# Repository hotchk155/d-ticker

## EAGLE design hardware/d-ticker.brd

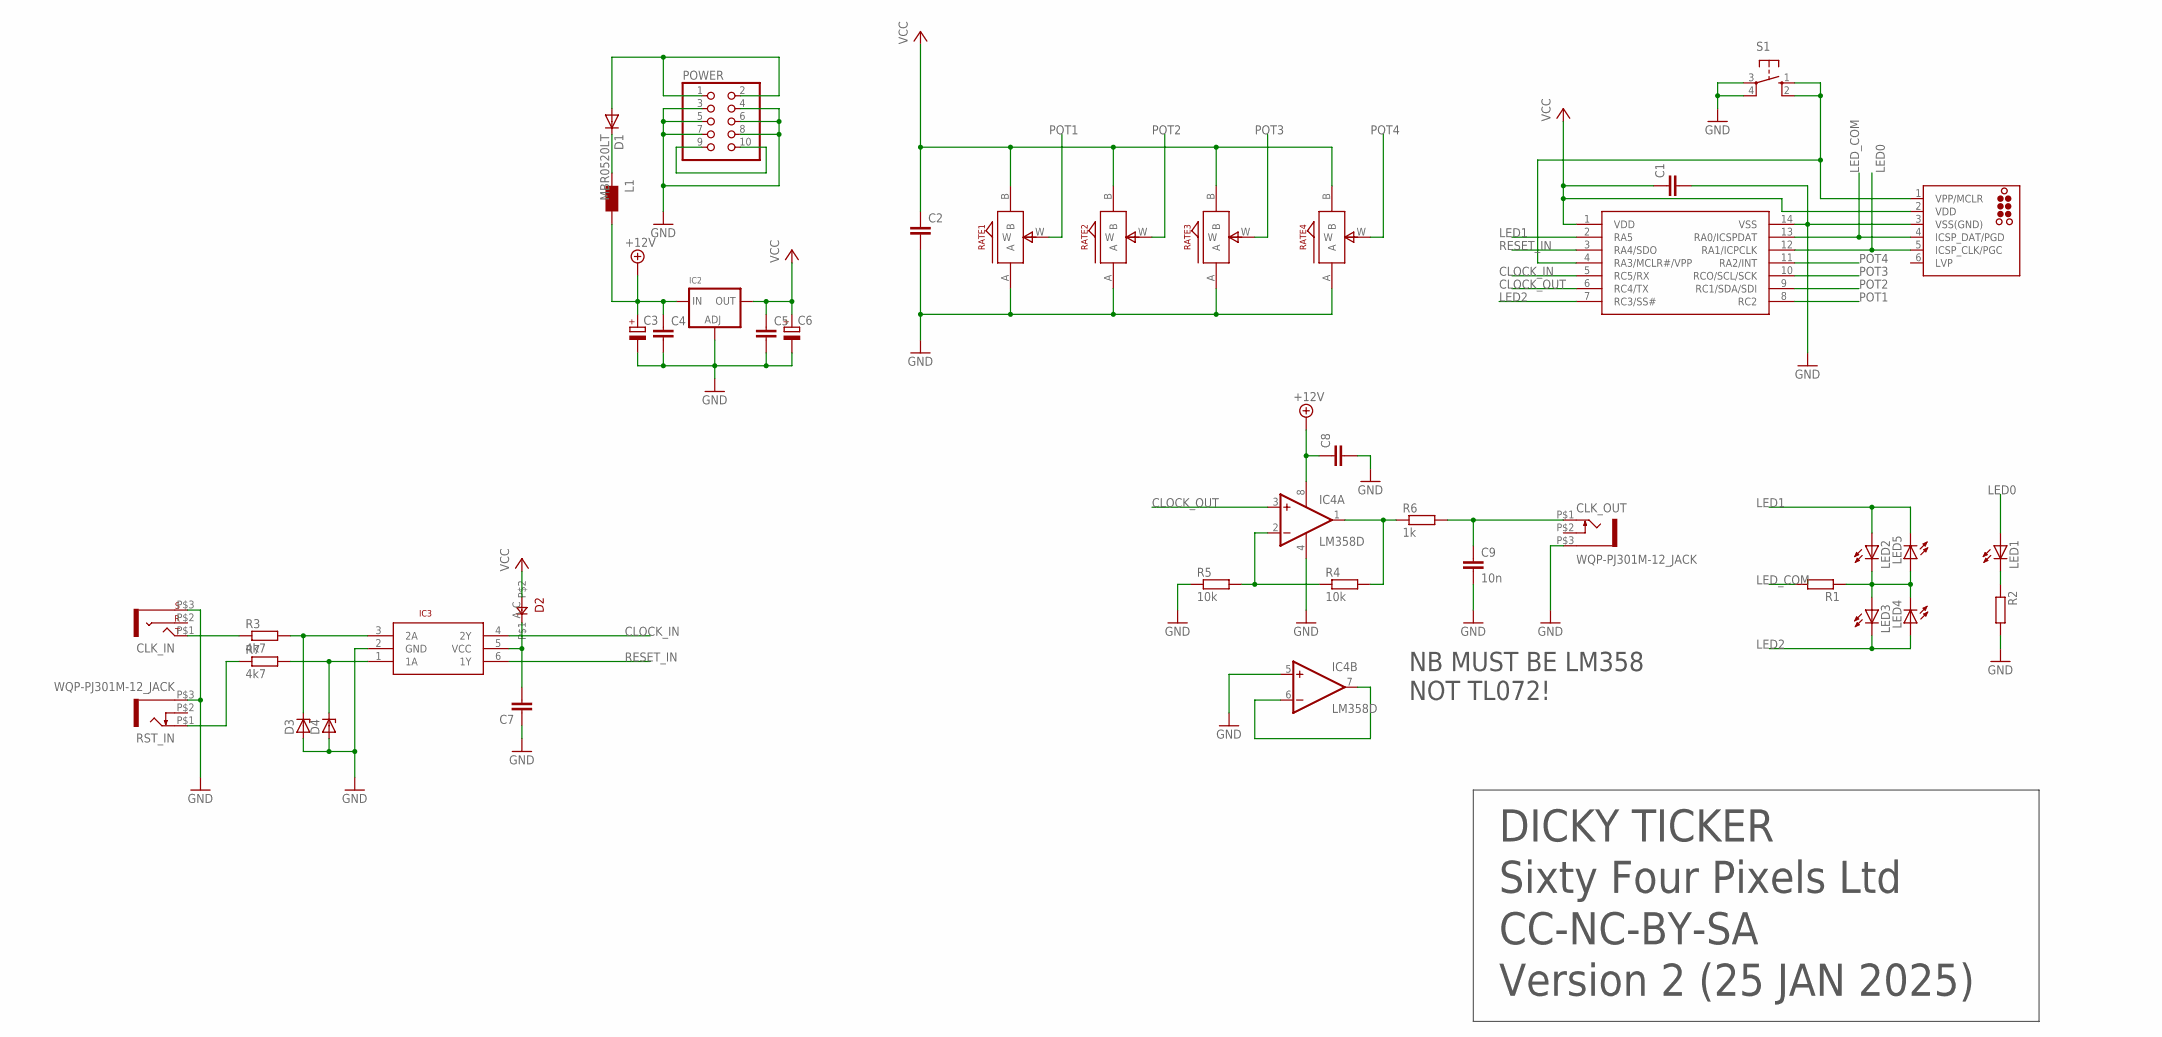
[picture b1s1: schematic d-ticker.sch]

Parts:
C1, C2, C4, C5, C7, C8: C-EUC0805; C0805
C3, C6: CPOL-EUSMCA; SMC_A
C9: 10n; C0805
CLK_IN: THONKICONN_STEREO; WQP-PJ301M-ST
CLK_OUT: WQP-PJ301M-12_JACK
D1: MBR0520LT; SOD123
D2: 0805DIODE
D3, D4: ZENER-DIODESOD80C; SOD80C
IC1: PIC16F1825SO14; SO14
IC2: LM1117SOT223-WAVE; SOT223-W
IC3: SN74LVC2G14; DBV_R-PDSO-G6
IC4: LM358D; SO08
ICSP: TC2030-MCP-NL
L1: WE-CBF_0805; 0805
LED1, LED2, LED3, LED4, LED5: LED3MM
POWER: PINHD-2X5; 2X05
R1, R2: R-EU_R0805; R0805
R3, R7: 4k7; R0805
R4, R5: 10k; R0805
R6: 1k; R0805
RATE1, RATE2, RATE3, RATE4: ALPS_POT_SMALL; SMALL_ALPS_POT
RST_IN: WQP-PJ301M-12_JACK
S1: 10-XX; B3F-10XX

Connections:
+12V: C3.+, C4.1, C8.1, IC2.3 (IN), IC4.8 (V+), L1.2
CLOCK_IN: IC1.5 (RC5/RX), IC3.4 (2Y)
CLOCK_OUT: IC1.6 (RC4/TX), IC4.3 (+IN)
GND: C1.2, C2.2, C3.-, C4.2, C5.2, C6.-, C7.1, C8.2, C9.2, CLK_IN.P$3 (S), CLK_OUT.P$3 (1), D3.A, D4.A, IC1.14 (VSS), IC2.1 (ADJ), IC3.2 (GND), IC4.4 (V-), IC4.5 (+IN), ICSP.3 (VSS(GND)), POWER.3, POWER.4, POWER.5, POWER.6, POWER.7, POWER.8, R2.2, R5.1, RATE1.A, RATE2.A, RATE3.A, RATE4.A, RST_IN.P$3 (1), S1.3, S1.4 (P1)
LED0: IC1.12 (RA1/ICPCLK), ICSP.5 (ICSP_CLK/PGC), LED1.A
LED1: IC1.2 (RA5), LED2.A, LED5.K (C)
LED2: IC1.7 (RC3/SS#), LED3.K (C), LED4.A
LED_COM: IC1.13 (RA0/ICSPDAT), ICSP.4 (ICSP_DAT/PGD), R1.2
unnamed: CLK_IN.P$1 (T), R3.1
unnamed: C7.2, D2.A, IC3.5 (VCC)
unnamed: IC4.2 (-IN), R4.1, R5.2
unnamed: R7.1, RST_IN.P$1 (2)
unnamed: IC4.6 (-IN), IC4.7 (OUT)
unnamed: LED1.K (C), R2.1
unnamed: IC4.1 (OUT), R4.2, R6.1
unnamed: C9.1, CLK_OUT.P$1 (2), R6.2
unnamed: POWER.9, POWER.10
unnamed: D1.A, POWER.1, POWER.2
unnamed: LED2.K (C), LED3.A, LED4.K (C), LED5.A, R1.1
unnamed: D1.C, L1.1
unnamed: D3.C, IC3.3 (2A), R3.2
unnamed: D4.C, IC3.1 (1A), R7.2
unnamed: IC1.4 (RA3/MCLR#/VPP), ICSP.1 (VPP/MCLR), S1.1 (S), S1.2 (S1)
POT1: IC1.8 (RC2), RATE1.W
POT2: IC1.9 (RC1/SDA/SDI), RATE2.W
POT3: IC1.10 (RCO/SCL/SCK), RATE3.W
POT4: IC1.11 (RA2/INT), RATE4.W
RESET_IN: IC1.3 (RA4/SDO), IC3.6 (1Y)
VCC: C1.1, C2.1, C5.1, C6.+, D2.C, IC1.1 (VDD), IC2.2 (OUT), ICSP.2 (VDD), RATE1.B, RATE2.B, RATE3.B, RATE4.B

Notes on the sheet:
DICKY TICKER
Sixty Four Pixels Ltd
CC-NC-BY-SA
Version 2 (25 JAN 2025)
NB MUST BE LM358 NOT TL072!

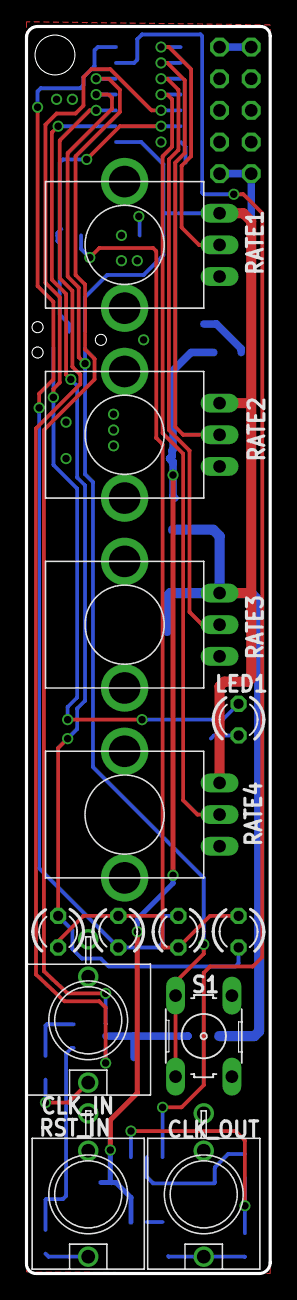
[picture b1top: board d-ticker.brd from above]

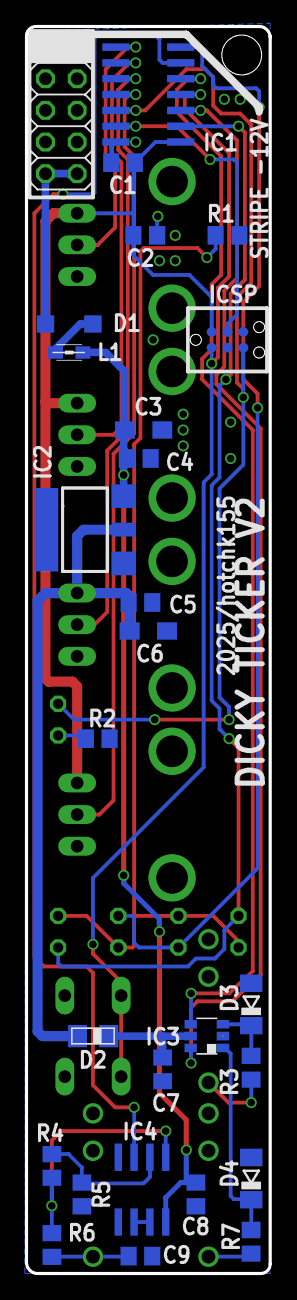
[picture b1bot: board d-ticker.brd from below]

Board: 2 copper layers, 19.6 x 100.1 mm, 40 parts (27 on the bottom side), 29 nets.

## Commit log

2021-12-26 sdfdsfa
2022-01-15 sdds
2022-03-01 asasasas
2024-12-01 dasads
2024-12-12 dsfsdf
2024-12-14 dsfsdsf
2024-12-14 dssdf
2024-12-17 asdasdd
2024-12-20 sfddf
2024-12-20 fdsfds
2024-12-20 dsfdsff
2025-01-24 turn mcu
2025-01-25 various changes per prototype
2025-03-30 pcb rev 2

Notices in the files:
parts and their libraries:
tag-connect: ©2009 ROFA.cz - modified and updated by Robert Darlington ‹rdarlington@gmail.com›
wuerth-elektronik: Copyright: Würth Elektronik eiSos
